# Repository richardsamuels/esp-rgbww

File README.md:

# esp32-rgbww
This is a custom ESP32-based LED controller that easily links with
ESPhome and Home Assistant.

The device has 5 low-side MOSFETs for controlling LEDs up to 24V. Terminal block
rated for 8A of current, barrel jack rated for 6A. Device must be flashed
using a Tag-Connect TC2030-USB-NL cable. Two config files are available.

## PCB and Pinout

### GPIO Pin Index

| Labeled Pin | GPIO Pin |
| ----------- | -------- |
| R           | 10       |
| G           | 7        |
| B           | 6        |
| CW          | 5        |
| WW          | 3        |
| D0          | 28       |
| D1          | 27       |
| ADC         | 4        |

## 3D Printed Case

3D Printable parts are available in the STL directory. These parts should be
printed from a plastic capable of withstanding 70C internal temperatures (ABS
recommended). An M2 bolt can be used to secure the case together, however care
should be used as the female end is vulnerable to cracking.

## Configuration

### 2channel-monochrome.yaml
Provides 2 independent channels of monochrome LED support (trivially extendable
to 5).

### rgbww.yaml
Provides 5 channels of LED support, intended for 6 wire LED strips (RGB, CW,
WW).

Exposed to ESPhome/Home Assistant as a RGBWW light with color interlock
enabled.

## Future Work
1. The case's screw hole can crack if over-torqued, or if the print is of low
quality. A future revision should allow for a larger female end to avoid cracks
and layer separation while screwing the case halves together.
2. The PWM frequency can cause visible artifacts on rolling shutter cameras. 
Experiment with the PWM frequency and capacitors to reduce these artifacts
3. Due to gate capacitance, the LEDs can take up two seconds to respond to
"turn off" signals. Use a proper gate driver circuit for the MOSFETs

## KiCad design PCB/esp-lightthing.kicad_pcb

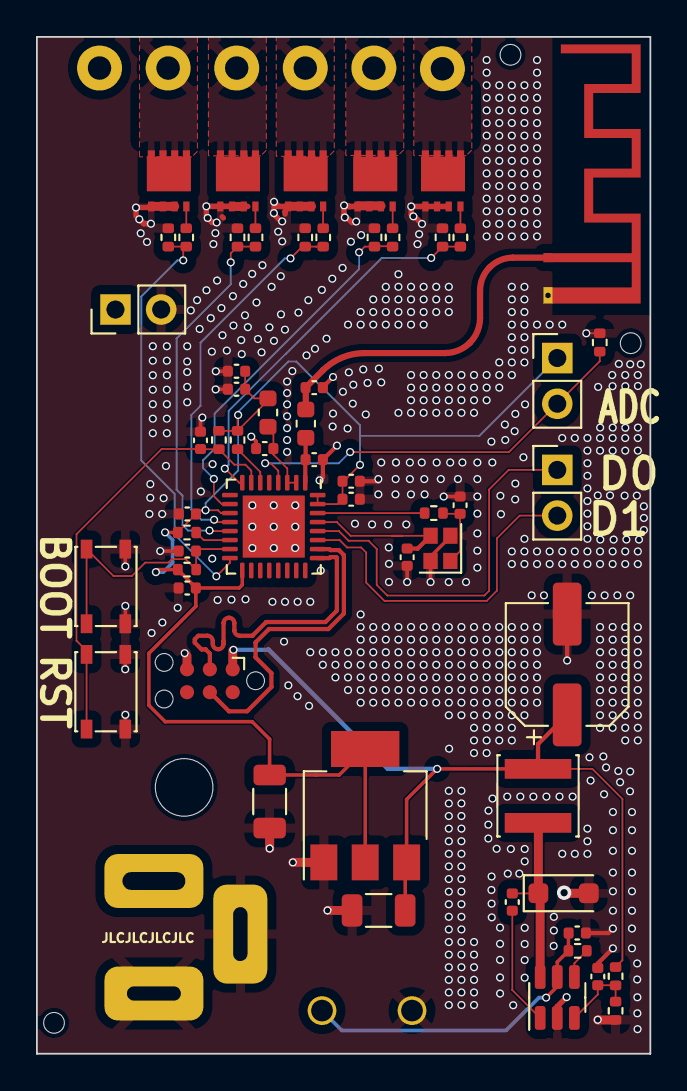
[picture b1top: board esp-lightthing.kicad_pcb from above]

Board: 4 copper layers, 34.1 x 56.5 mm, 61 parts (0 on the bottom side), 38 nets.

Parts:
AE301: 2.4GHz aerial; Texas_SWRA117D_2.4GHz_Left
C101: DNP; PinHeader_1x02_P2.54mm_Vertical
C201, C202: CL05B104KB54PNC; C_0402_1005Metric
C203: 0402CG200J500NT; C_0402_1005Metric
C204: VES220M1HTR-0605; CP_Elec_6.3x5.3
C205, C206: 22uF; C_1206_3216Metric
C301, C302: 3p3; C_0402_1005Metric
C303, C304: 100n; C_0402_1005Metric
C305: 1u; C_0402_1005Metric
C306: 10n; C_0402_1005Metric
C307: 10u; C_0402_1005Metric
C308, C309, C310, C311: 0.1u; C_0402_1005Metric
C312, C313: 12p; C_0402_1005Metric
D201: DSS14; D_SOD-123F
J101: Conn_01x06_Socket; WJ124-3.81-6P
J102, J103: Conn_01x02_Pin; PinHeader_1x02_P2.54mm_Vertical
J201: 12V 7.5A; DC-005H-D025
J202: 12-24V; WJ126V-5.0-2P
J203: USB_TC2030-USB-NL; Tag-Connect_TC2030-IDC-NL_2x03_P1.27mm_Vertical
L201: FNR4012S220MT; L_Changjiang_FNR4012S
L301, L302: 2n2; L_0603_1608Metric
Q201, Q202, Q203, Q204, Q205: WSD3070DN
R101, R301, R302, R304, R305: 5k1; R_0402_1005Metric
R201: 0402WGF4992TCE; R_0402_1005Metric
R202: RM04FTN9531; R_0402_1005Metric
R203, R205, R207, R209, R211, R213: 100R; R_0402_1005Metric
R204, R206, R208, R210, R212: 100k; R_0402_1005Metric
R303: 0; R_0402_1005Metric
SW301, SW302: SW_Push; SW_SPST_PTS810
U1: ESP32-C3FN4; QFN-32-1EP_5x5mm_P0.5mm_EP3.45x3.45mm
U201: AOZ1282CI; SOT-23-6
U202: LDL111733R; SOT-223-3_TabPin2
Y1: Crystal_GND24; Crystal_SMD_2016-4Pin_2.0x1.6mm

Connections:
+3V3: C206.1, C305.1, C306.1, C307.1, C308.1, C310.1, C311.1, J102.1, L302.1, R301.1, R302.1, R304.2, R305.2, U1.11 (VDD3P3_RTC), U1.17 (VDD3P3_CPU), U1.31 (VDDA), U1.32 (VDDA), U202.2 (VO)
+5V: C204.1, C205.1, J203.1 (VBUS), L201.2, R201.2, U202.3 (VI)
/ADC: J102.2, R101.1, U1.4 (XTAL_32K_P/ADC1_CH0)
/D0: J103.1, U1.28 (U0TXD/GPIO21)
/D1: J103.2, U1.27 (U0RXD/GPIO20)
/ESP32/BOOT: C304.1, R302.2, SW302.2, U1.15 (GPIO9/BOOT)
/ESP32/D+: J203.4 (D+), U1.26 (GPIO19/USB_D+)
/ESP32/D-: J203.3 (D-), U1.25 (GPIO18/USB_D-)
/ESP32/GATE_B: R207.1, R208.1, U1.12 (MTCK/GPIO6)
/ESP32/GATE_CW: R209.1, R210.1, U1.10 (MTDI/GPIO5/ADC2_CH0)
/ESP32/GATE_G: R205.1, R206.1, U1.13 (MTDO/GPIO7)
/ESP32/GATE_R: R203.1, R204.1, U1.16 (GPIO10)
/ESP32/GATE_WW: R211.1, R212.1, U1.8 (GPIO3/ADC1_CH3)
/ESP32/LNA: C302.1, L301.2, U1.1 (LNA_IN)
/ESP32/LNA_Z=50: AE301.1 (FEED), C301.1, L301.1
/ESP32/RESET: C303.1, R301.2, SW301.2, U1.7 (CHIP_EN)
/ESP32/VDD3P3: C309.1, L302.2, U1.2 (VDD3P3), U1.3 (VDD3P3)
/ESP32/XTAL_N: C313.1, U1.29 (XTAL_N), Y1.3
/ESP32/XTAL_P: R303.1, U1.30 (XTAL_P)
/power/B: J101.4, Q203.3 (D)
/power/CW: J101.5, Q204.3 (D)
/power/G: J101.3, Q202.3 (D)
/power/LX_5V: C202.1, D201.1 (K), L201.1, U201.6 (LX)
/power/R: J101.2, Q201.3 (D)
/power/WW: J101.6, Q205.3 (D)
GND: AE301.2 (PCB_Trace), C101.2, C201.2, C203.2, C204.2, C205.2, C206.2, C301.2, C302.2, C303.2, C304.2, C305.2, C306.2, C307.2, C308.2, C309.2, C310.2, C311.2, C312.2, C313.2, D201.2 (A), J201.2, J202.2, J203.5 (GND), Q201.1 (S), Q202.1 (S), Q203.1 (S), Q204.1 (S), Q205.1 (S), R101.2, R202.2, R204.2, R206.2, R208.2, R210.2, R212.2, SW301.1, SW302.1, U1.33 (GND), U201.2 (GND), U202.1 (GND), Y1.2, Y1.4
unnamed: C312.1, R303.2, Y1.1
unnamed: Q201.2 (G), R203.2
unnamed: Q202.2 (G), R205.2
unnamed: Q203.2 (G), R207.2
unnamed: Q204.2 (G), R209.2
unnamed: Q205.2 (G), R211.2
unnamed: R304.1, U1.6 (GPIO2/ADC1_CH2)
unnamed: R305.1, U1.14 (GPIO8)
unnamed: C202.2, U201.1 (BST)
unnamed: R213.1, U201.4 (EN)
unnamed: C203.1, R201.1, R202.1, U201.3 (FB)
VCC: C101.1, C201.1, J101.1, J201.1, J202.1, R213.2, U201.5 (VIN)

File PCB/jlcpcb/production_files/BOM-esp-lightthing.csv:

Comment,Designator,Footprint,LCSC
AOZ1282CI,U201,SOT-23-6,C111916
WSD3070DN,"Q201,Q202,Q203,Q204,Q205",WSD3070DN,C148387
10n,C306,C_0402_1005Metric,C15195
12p,"C312,C313",C_0402_1005Metric,C1547
10u,C307,C_0402_1005Metric,C15525
0402CG200J500NT,C203,C_0402_1005Metric,C1554
3p3,"C301,C302",C_0402_1005Metric,C1565
FNR4012S220MT,L201,L_Changjiang_FNR4012S,C167789
0,R303,R_0402_1005Metric,C17168
RM04FTN9531,R202,R_0402_1005Metric,C173840
VES220M1HTR-0605,C204,CP_Elec_6.3x5.3,C176676
100R,"R203,R205,R207,R209,R211,R213",R_0402_1005Metric,C25076
Crystal_GND24,Y1,Crystal_SMD_2016-4Pin_2.0x1.6mm,C255898
100k,"R204,R206,R208,R210,R212",R_0402_1005Metric,C25741
0402WGF4992TCE,R201,R_0402_1005Metric,C25897
5k1,"R301,R302,R304,R305",R_0402_1005Metric,C25905
2n2,"L301,L302",L_0603_1608Metric,C29682
CL05B104KB54PNC,"C201,C202,C303,C304,C308,C309,C310,C311",C_0402_1005Metric,C307331
LDL111733R,U202,SOT-223-3_TabPin2,C435835
SW_Push,"SW301,SW302",SW_SPST_PTS810,C470426
ESP32-C3FN4,U1,QFN-32-1EP_5x5mm_P0.5mm_EP3.45x3.45mm,C5143572
1u,C305,C_0402_1005Metric,C52923
12V 7.5A,J201,DC-005H-D025,C5353839
22uF,"C205,C206",C_1206_3216Metric,C5672
DSS14,D201,D_SOD-123F,C59293
Conn_01x06_Socket,J101,WJ124-3.81-6P,C69810
12-24V,J202,WJ126V-5.0-2P,C8404
USB_TC2030-USB-NL,J203,Tag-Connect_TC2030-IDC-NL_2x03_P1.27mm_Vertical,
2.4GHz aerial,AE301,Texas_SWRA117D_2.4GHz_Left,
5k1,R101,R_0402_1005Metric,
Conn_01x02_Pin,J103,PinHeader_1x02_P2.54mm_Vertical,
Conn_01x02_Pin,J102,PinHeader_1x02_P2.54mm_Vertical,
DNP,C101,PinHeader_1x02_P2.54mm_Vertical,

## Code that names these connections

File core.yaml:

substitutions:
  name: "name"

esphome:
  name: "${name}"
  platformio_options:
    board_build.flash_mode: dio
    board_build.f_flash: 40000000L
    board_build.flash_size: 4MB
  on_boot:
    - priority: 500
      then:
        - esp32_ble_tracker.stop_scan:
    - priority: 100
      then:
        - delay: 10s
        - esp32_ble_tracker.start_scan:
            continuous: true

esp32:
  board: esp32-c3-devkitm-1
  variant: esp32c3
  framework:
    #type: arduino
    type: esp-idf

# Enable logging
logger:
  logs:
    esp-idf: ERROR

<<: !include secrets.yaml

esp32_ble_tracker:
  scan_parameters:
    active: true
    continuous: true

bluetooth_proxy:
  active: true

output:
  - platform: ledc
    id: output_r
    pin: GPIO10
    max_power: 80%
    min_power: 1%
    zero_means_zero: true
  - platform: ledc
    id: output_g
    pin: GPIO7
    max_power: 80%
    min_power: 1%
    zero_means_zero: true
  - platform: ledc
    id: output_b
    pin: GPIO6
    max_power: 80%
    min_power: 1%
    zero_means_zero: true
  - platform: ledc
    id: output_cw
    pin: GPIO5
    max_power: 80%
    min_power: 1%
    zero_means_zero: true
  - platform: ledc
    id: output_ww
    pin: GPIO3
    max_power: 80%
    min_power: 1%
    zero_means_zero: true

sensor:
  - platform: internal_temperature
    name: "ESP32 Die Temp"

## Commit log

2023-09-13 Hello World!
2024-01-25 Add photos, pinouts, and future work to README
2024-01-25 Add CI
2024-01-25 add template secrets.yaml
2024-01-25 ESPhome is picky
2024-01-26 Add photos, pinouts, and future work to README (#2)
